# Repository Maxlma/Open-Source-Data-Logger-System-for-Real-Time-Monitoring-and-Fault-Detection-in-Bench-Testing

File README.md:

# 🧠 Smart Power Supply for Data Loggers

**Low-Cost / High-Precision UPS for Reliable Data Acquisition Systems**  
[Published in *Energies*, MDPI - DOI: [10.3390/en16010278](https://doi.org/10.3390/en16010278)]

## 📌 About the Project

This project presents the design and implementation of a **smart, low-cost, and high-precision power supply** system tailored for **data loggers** in experimental setups. It provides **uninterruptible power**, advanced **monitoring features**, and a **DIY-friendly open hardware** approach with robust performance under demanding conditions.

Developed by researchers from the **University of São Paulo (USP)** and the **University of Minho**, this power supply ensures uninterrupted operation even during AC power failures, thanks to an embedded UPS and smart control logic.

## ⚙️ Features

- 🔋 **AC/DC Dual Input** with seamless switching (UPS functionality)
- 📶 **Serial communication (UART)** with external devices
- 📺 **OLED Display** for real-time system status
- 🌡️ **Temperature monitoring** and **smart active cooling**
- 🔄 **Remote firmware update capability**
- 📏 Outputs: ±12V, 5V, 3.3V – bipolar and unipolar DC
- 🛡️ Protection: 3 internal fuses for AC input, DC section, and battery
- 🧠 Controlled by an **ATmega328PB** microcontroller
- 🧩 Fully documented open hardware – easily 3D printable case
- 💸 **Total cost under $150**

## 🧪 Experimental Results

Tests confirmed:

- **Switching time < 10 ms** between power sources  
- No voltage drop affecting operation under 0A, 1A, and 2A loads  
- Stable operation under AC loss scenarios  
- Precise voltage regulation and thermal control

## 📜 License

This project is licensed under the **Creative Commons BY 4.0**  
© 2022 by the authors. Reuse permitted with attribution.  
[License Details](https://creativecommons.org/licenses/by/4.0/)

## 👨‍🔬 Authors

- Márcio L. M. Amorim  
- Gabriel A. Ginja  
- João P. Carmo  
- Melkzedekue M. A. Moreira  
- Adriano A. G. Siqueira  
- José A. Afonso

## 📚 Citation

If you use this work, please cite:

> Amorim, M.L.M.; Ginja, G.A.; Carmo, J.P.; Moreira, M.M.A.; Siqueira, A.A.G.; Afonso, J.A.  
> *Low-Cost/High-Precision Smart Power Supply for Data Loggers.*  
> Energies 2023, 16, 278. DOI: [10.3390/en16010278](https://doi.org/10.3390/en16010278)

---

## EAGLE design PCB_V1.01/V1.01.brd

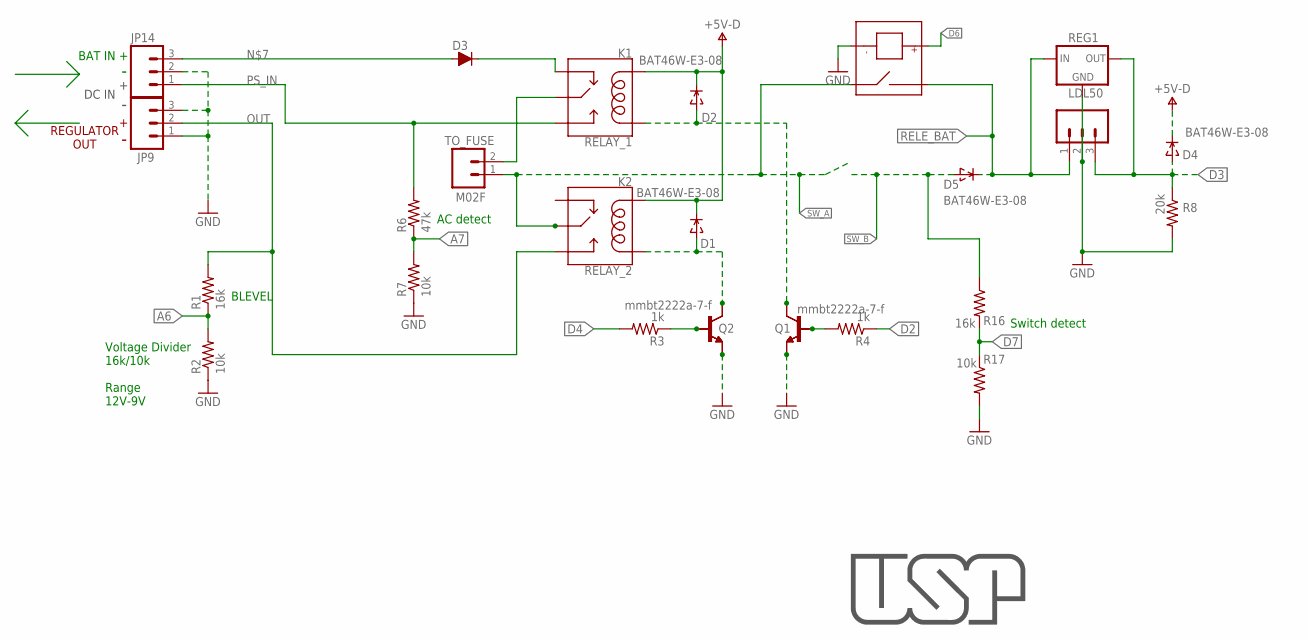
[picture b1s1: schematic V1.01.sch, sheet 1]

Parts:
7805: M03LOCK; 1X03_LOCK
D1, D2, D4, D5: BAT46W-E3-08; SOD-123
D3: DIODEFR; DIODE1.5A
JP9, JP14: M03; AK500
K1: RELAY_1; RELAY_G5LE
K2: RELAY_2; RELAY_G5LE
Q1, Q2: mmbt2222a-7-f; SOT23-3
Q3, Q4: TRANSISTOR-NPN-BC337; BC337
R1, R16: 16k; 0402
R2, R7, R17: 10k; 0402
R3, R4: 1k; 0402
R6: 47k; 0402
R8: 20k; 0402
REG1: LDL50; SOT223
RL1: RELAY_HE3621A0500; HE3621A
TO_FUSE: M02F; AK500M2

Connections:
+5V-D: D1.C, D2.C, D4.C, K1.2 (COIL1), K2.2 (COIL1); also elsewhere on the board
A6: R1.P$1 (1), R2.P$2 (2); also elsewhere on the board
A7: R6.P$1 (1), R7.P$2 (2); also elsewhere on the board
D2: R4.P$1 (1); also elsewhere on the board
D3: 7805.3, D4.A, R8.P$1 (1), REG1.2 (OUT), REG1.4 (OUT); also elsewhere on the board
D4: R3.P$2 (2); also elsewhere on the board
D6: RL1.P2; also elsewhere on the board
D7: R16.P$2 (2), R17.P$1 (1); also elsewhere on the board
GND: 7805.2, JP9.1, JP9.3, JP14.2, Q1.2 (E), Q2.2 (E), Q3.1 (E), Q4.1 (E), R2.P$1 (1), R7.P$1 (1), R8.P$2 (2), R17.P$2 (2), REG1.1 (GND), RL1.P3; also elsewhere on the board
unnamed: K1.1 (MAIN), TO_FUSE.2
unnamed: D2.A, K1.5 (COIL2), Q1.3 (C), Q4.3 (C)
unnamed: D1.A, K2.5 (COIL2), Q2.3 (C), Q3.3 (C)
unnamed: D3.A, JP14.3
unnamed: Q1.1 (B), Q4.2 (B), R4.P$2 (2)
unnamed: D3.C, K1.4 (NC)
OUT: JP9.2, K2.3 (NO), R1.P$2 (2)
PS_IN: JP14.1, K1.3 (NO), R6.P$2 (2)
RELE_BAT: 7805.1, D5.C, REG1.3 (IN), RL1.P1; also elsewhere on the board
STARTUP: Q2.1 (B), Q3.2 (B), R3.P$1 (1)
SW_A: K2.1 (MAIN), RL1.P4, TO_FUSE.1; also elsewhere on the board
SW_B: D5.A, R16.P$1 (1); also elsewhere on the board

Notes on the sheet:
BLEVEL
AC detect
Switch detect
BAT IN
REGULATOR OUT
DC IN
Voltage Divider 16k/10k Range 12V-9V

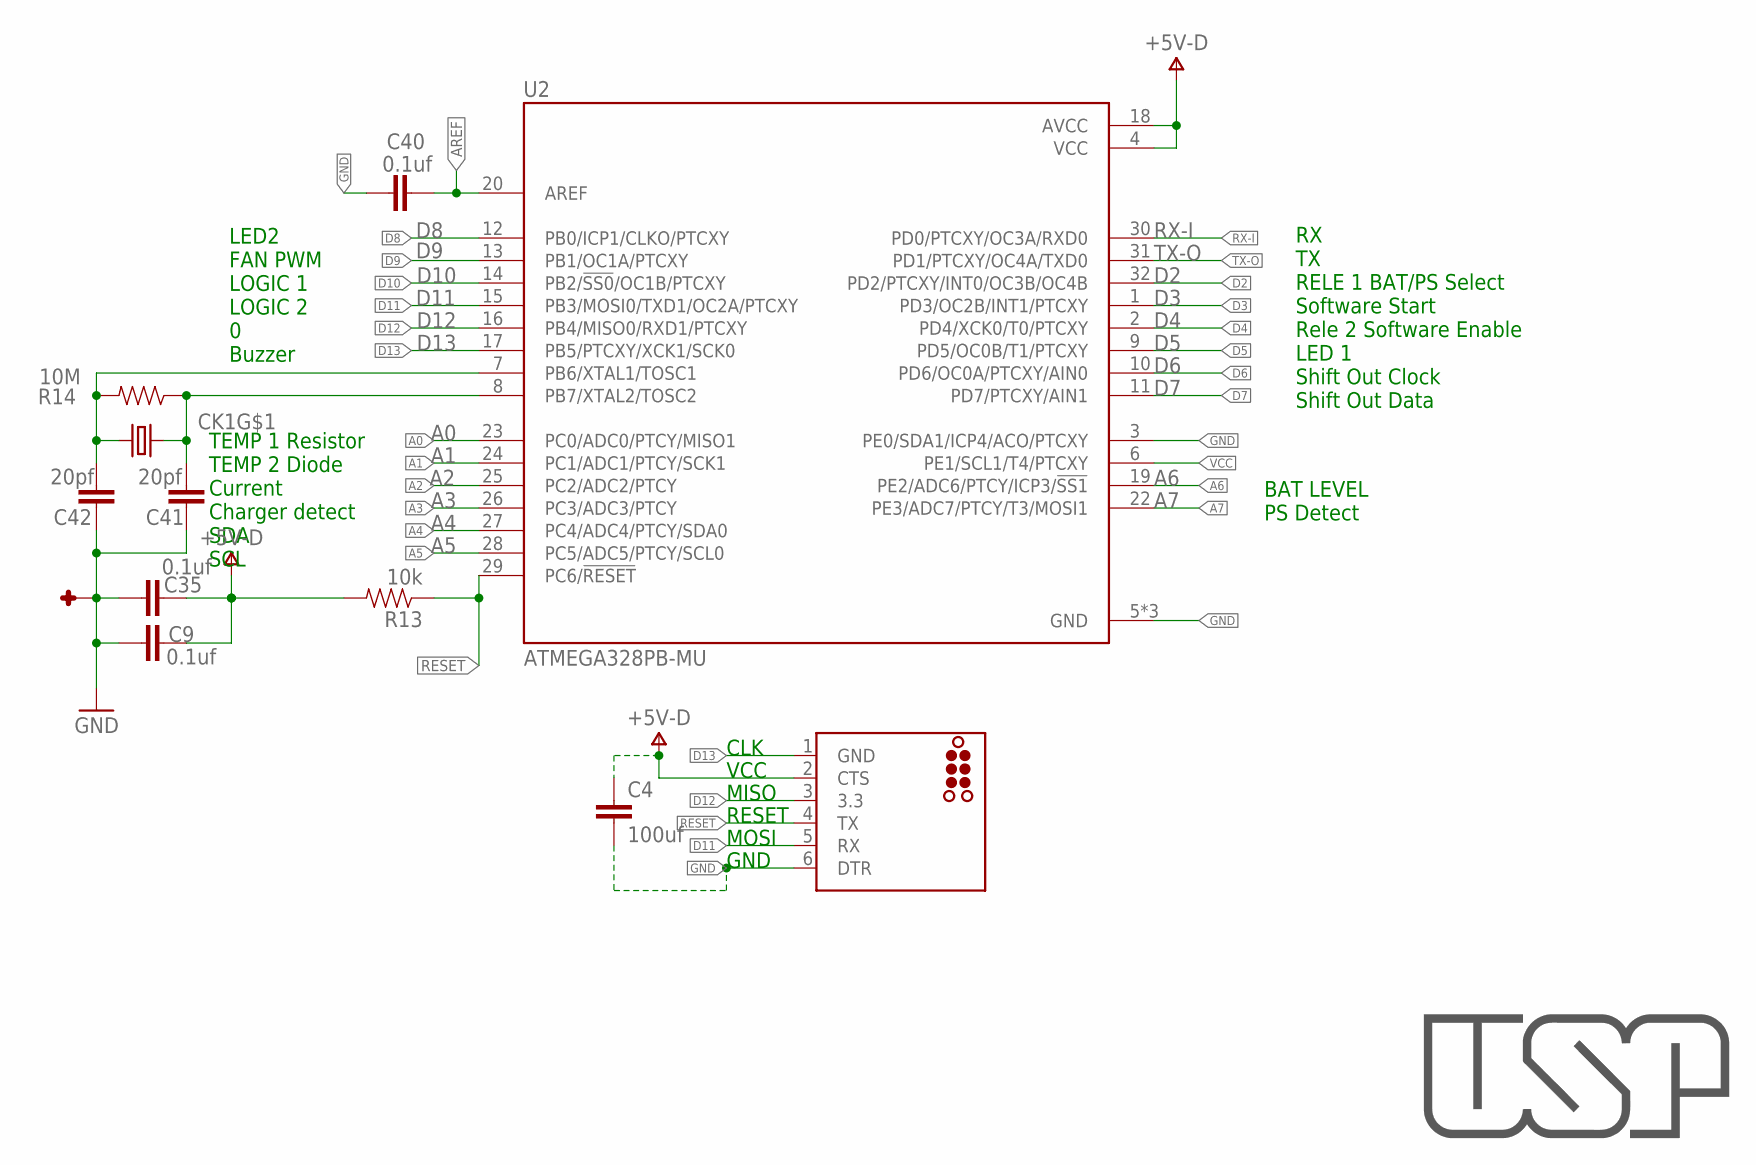
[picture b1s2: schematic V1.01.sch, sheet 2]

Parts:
C4: 100uf; 1206
C9, C35, C40: 0.1uf; 0402
C41, C42: 20pf; 0402
CK1: FA-238 16.0000MB-C3; 4-SMD@1
J10: DNP; TC2030-MCP-NL
R13: 10k; 0402
R14: 10M; 0402
U2: ATMEGA328PB-MU; QFN50P500X500X90-33N

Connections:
+5V-D: C4.1, C9.P$2 (2), C35.P$2 (2), J10.2 (CTS), R13.P$2 (2), U2.4 (VCC), U2.18 (AVCC); also elsewhere on the board
A0: U2.23 (PC0/ADC0/PTCY/MISO1); also elsewhere on the board
A1: U2.24 (PC1/ADC1/PTCY/SCK1); also elsewhere on the board
A2: U2.25 (PC2/ADC2/PTCY); also elsewhere on the board
A3: U2.26 (PC3/ADC3/PTCY); also elsewhere on the board
A4: U2.27 (PC4/ADC4/PTCY/SDA0); also elsewhere on the board
A5: U2.28 (PC5/ADC5/PTCY/SCL0); also elsewhere on the board
A6: U2.19 (PE2/ADC6/PTCY/ICP3/!SS1!); also elsewhere on the board
A7: U2.22 (PE3/ADC7/PTCY/T3/MOSI1); also elsewhere on the board
AREF: C40.P$1 (1), U2.20 (AREF)
D2: U2.32 (PD2/PTCXY/INT0/OC3B/OC4B); also elsewhere on the board
D3: U2.1 (PD3/OC2B/INT1/PTCXY); also elsewhere on the board
D4: U2.2 (PD4/XCK0/T0/PTCXY); also elsewhere on the board
D5: U2.9 (PD5/OC0B/T1/PTCXY)
D6: U2.10 (PD6/OC0A/PTCXY/AIN0); also elsewhere on the board
D7: U2.11 (PD7/PTCXY/AIN1); also elsewhere on the board
D8: U2.12 (PB0/ICP1/CLKO/PTCXY)
D9: U2.13 (PB1/OC1A/PTCXY); also elsewhere on the board
D10: U2.14 (PB2/!SS0!/OC1B/PTCXY)
D11: J10.5 (RX), U2.15 (PB3/MOSI0/TXD1/OC2A/PTCXY); also elsewhere on the board
D12: J10.3 (3.3), U2.16 (PB4/MISO0/RXD1/PTCXY)
D13: J10.1 (GND), U2.17 (PB5/PTCXY/XCK1/SCK0); also elsewhere on the board
GND: C4.2, C9.P$1 (1), C35.P$1 (1), C40.P$2 (2), C41.P$2 (2), C42.P$2 (2), CK1.GND1 (1), CK1.GND2 (1), J10.6 (DTR), U2.3 (PE0/SDA1/ICP4/ACO/PTCXY), U2.5 (GND), U2.21 (GND), U2.33 (GND); also elsewhere on the board
unnamed: C41.P$1 (1), CK1.P1 (1), R14.P$1 (1), U2.8 (PB7/XTAL2/TOSC2)
unnamed: C42.P$1 (1), CK1.P3 (2), R14.P$2 (2), U2.7 (PB6/XTAL1/TOSC1)
RESET: J10.4 (TX), R13.P$1 (1), U2.29 (PC6/!RESET!); also elsewhere on the board
RX-I: U2.30 (PD0/PTCXY/OC3A/RXD0); also elsewhere on the board
TX-O: U2.31 (PD1/PTCXY/OC4A/TXD0); also elsewhere on the board
VCC: U2.6 (PE1/SCL1/T4/PTCXY)

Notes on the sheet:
D11
RX TX RELE 1 BAT/PS Select Software Start Rele 2 Software Enable LED 1 Shift Out Clock Shift Out Data
LED2 FAN PWM LOGIC 1 LOGIC 2 0 Buzzer
TEMP 1 Resistor TEMP 2 Diode Current Charger detect SDA SCL
BAT LEVEL PS Detect
CLK VCC MISO RESET MOSI GND

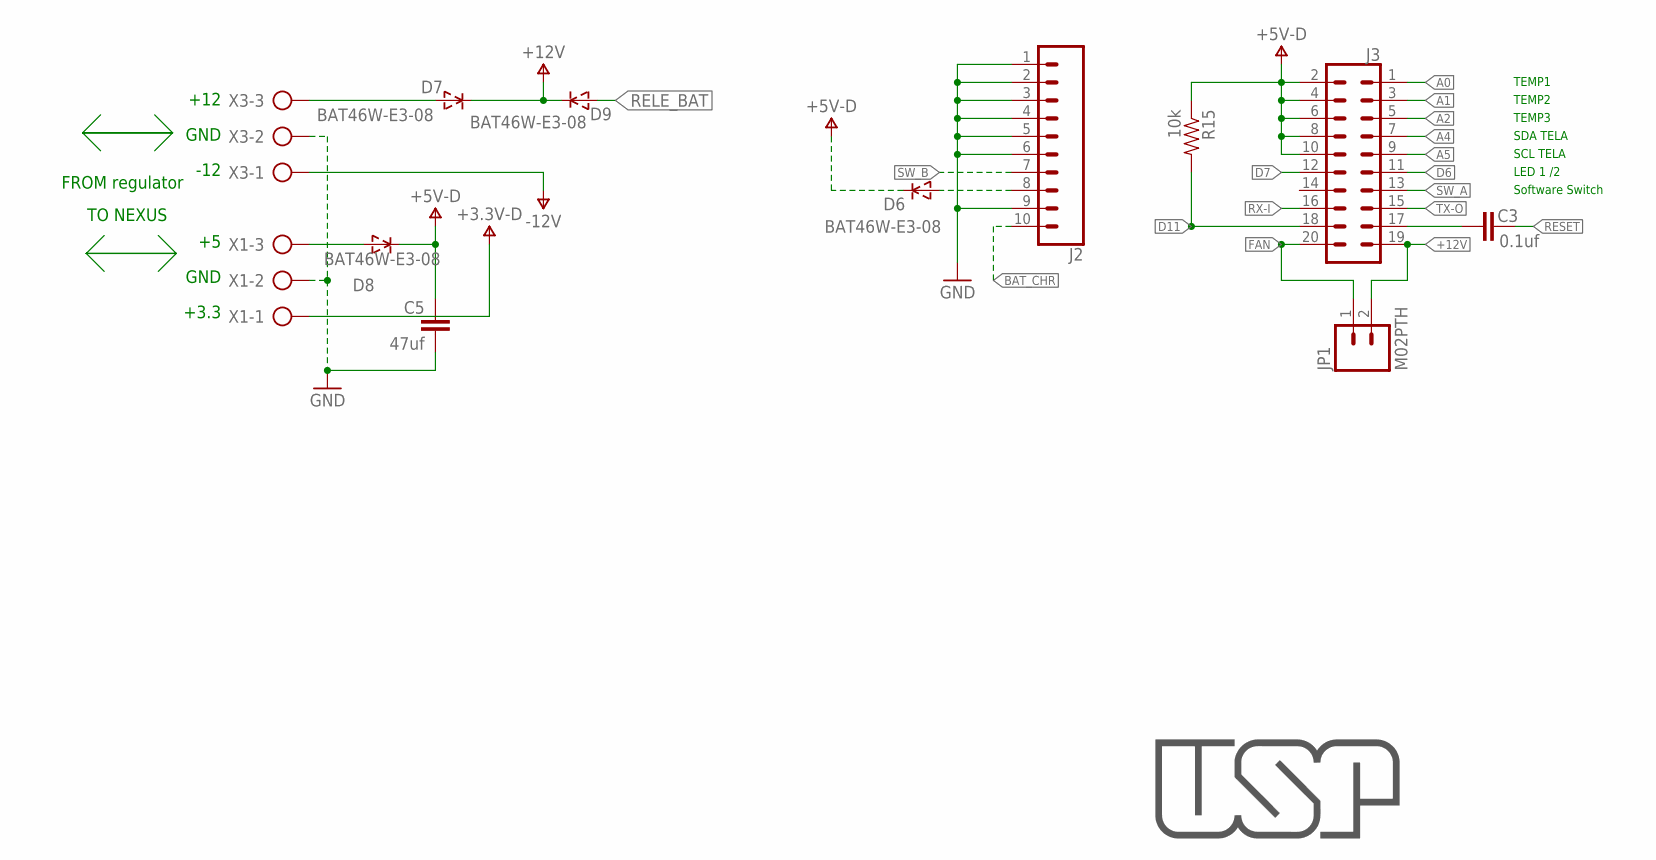
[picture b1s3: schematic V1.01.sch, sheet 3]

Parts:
C3: 0.1uf; 0402
C5: 47uf; 1206
D6, D7, D8, D9: BAT46W-E3-08; SOD-123
J2: CONN_10"; 1X10
J3: CONN_10X2; 2X10
JP1: M02PTH; 1X02
R15: 10k; 0402
X1, X3: AK500/3-H

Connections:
+3.3V-D: X1.1
+5V-D: C5.1, D6.C, D8.C, J3.2, J3.4, J3.6, J3.8, J3.10, R15.P$1 (1); also elsewhere on the board
+12V: D7.C, D9.C, J3.19, JP1.2
-12V: X3.1
A0: J3.1; also elsewhere on the board
A1: J3.3; also elsewhere on the board
A2: J3.5; also elsewhere on the board
A4: J3.7; also elsewhere on the board
A5: J3.9; also elsewhere on the board
BAT_CHR: J2.10; also elsewhere on the board
D6: J3.11; also elsewhere on the board
D7: J3.12; also elsewhere on the board
D11: J3.18, R15.P$2 (2); also elsewhere on the board
FAN: J3.20, JP1.1; also elsewhere on the board
GND: C5.2, J2.1, J2.2, J2.3, J2.4, J2.5, J2.6, J2.9, X1.2, X3.2; also elsewhere on the board
unnamed: D8.A, X1.3
unnamed: D6.A, J2.8
unnamed: D7.A, X3.3
RELE_BAT: D9.A; also elsewhere on the board
RESET: C3.P$2 (2); also elsewhere on the board
RESETT: C3.P$1 (1), J3.17
RX-I: J3.16; also elsewhere on the board
SW_A: J3.13; also elsewhere on the board
SW_B: J2.7; also elsewhere on the board
TX-O: J3.15; also elsewhere on the board

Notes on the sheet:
FROM regulator
+12 GND -12
TO NEXUS
TEMP1 TEMP2 TEMP3 SDA TELA SCL TELA LED 1 /2 Software Switch
+5 GND +3.3

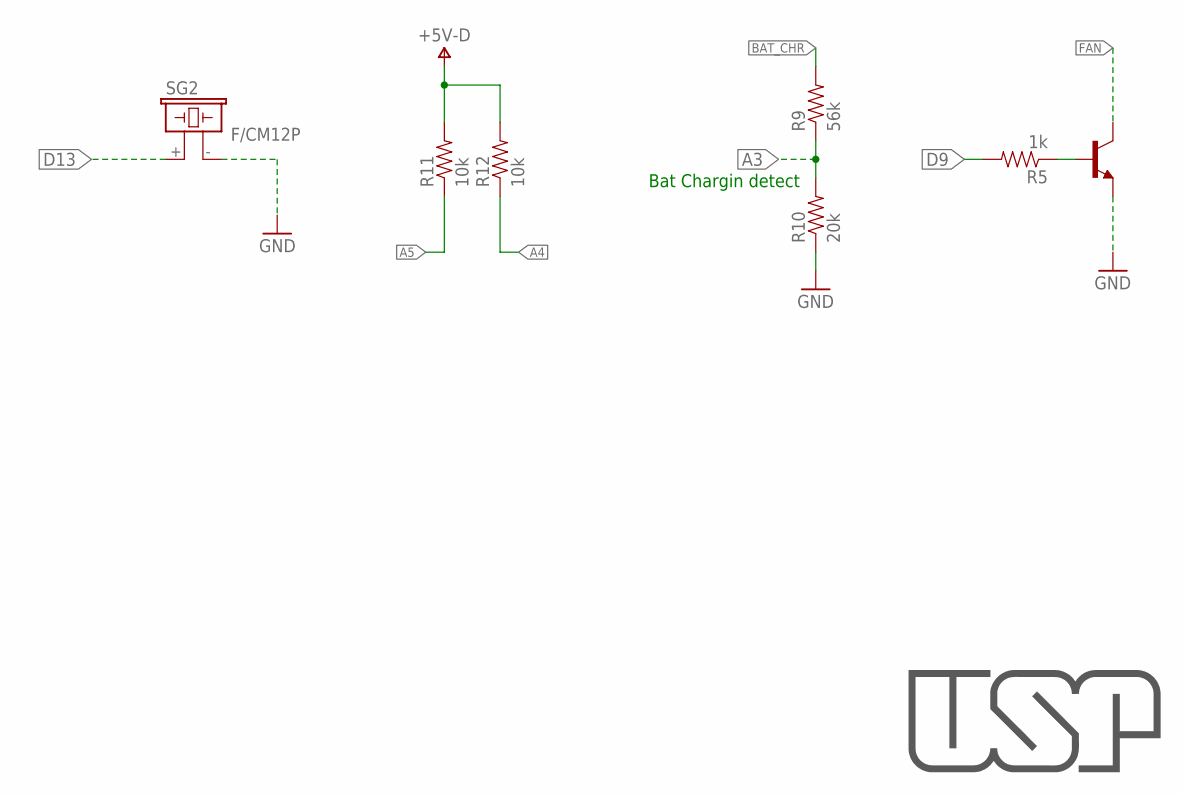
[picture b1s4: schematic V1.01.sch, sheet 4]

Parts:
Q5: TRANSISTOR-NPN-BC337; BC337
R5: 1k; 0402
R9: 56k; 0402
R10: 20k; 0402
R11, R12: 10k; 0402
SG2: F/CM12P

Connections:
+5V-D: R11.P$2 (2), R12.P$2 (2); also elsewhere on the board
A3: R9.P$1 (1), R10.P$2 (2); also elsewhere on the board
A4: R12.P$1 (1); also elsewhere on the board
A5: R11.P$1 (1); also elsewhere on the board
BAT_CHR: R9.P$2 (2); also elsewhere on the board
D9: R5.P$2 (2); also elsewhere on the board
D13: SG2.+ (1); also elsewhere on the board
FAN: Q5.3 (C); also elsewhere on the board
GND: Q5.1 (E), R10.P$1 (1), SG2.- (2); also elsewhere on the board
unnamed: Q5.2 (B), R5.P$1 (1)

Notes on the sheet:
Bat Chargin detect

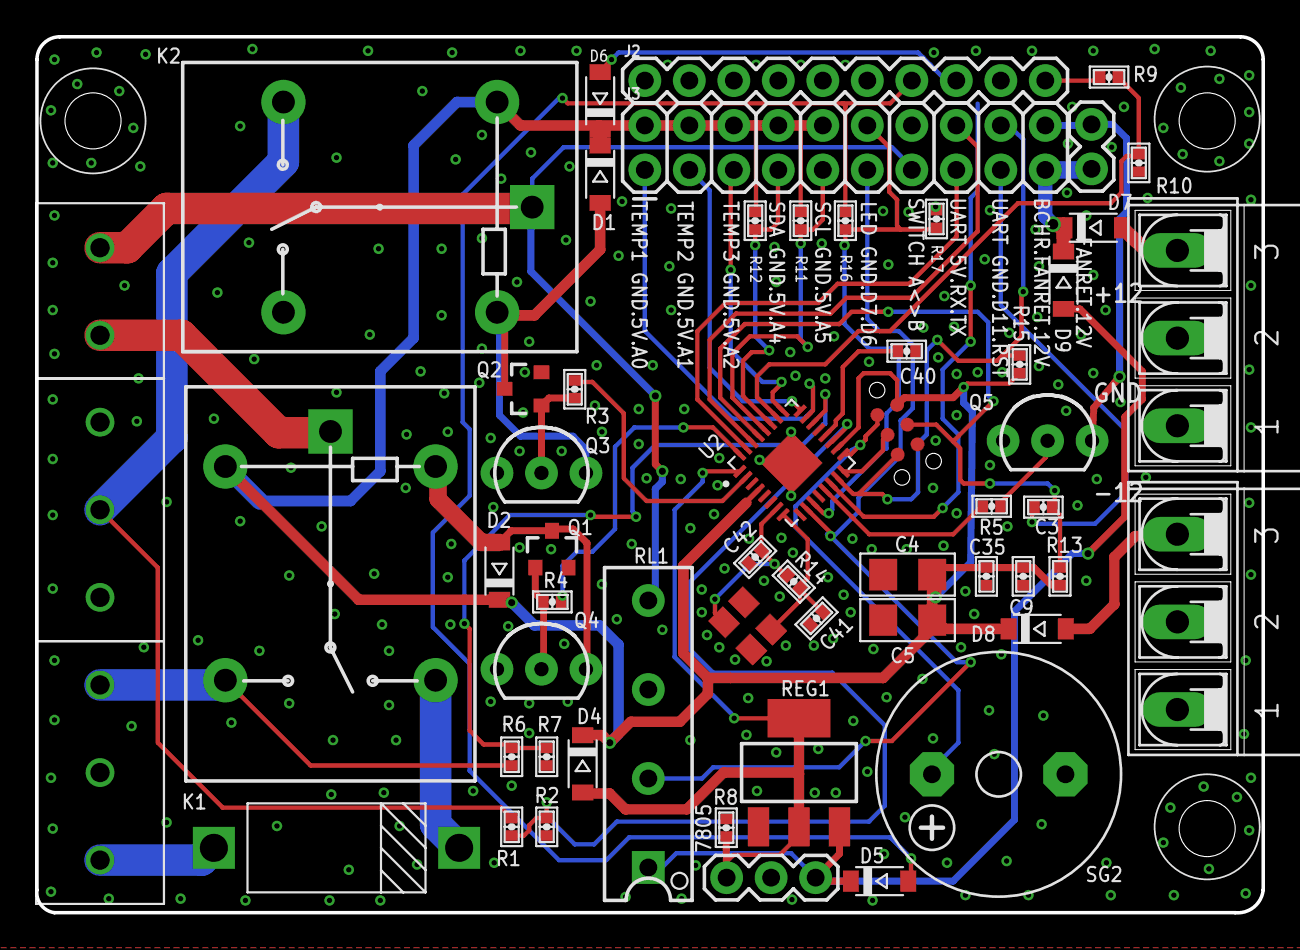
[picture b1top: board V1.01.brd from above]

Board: 2 copper layers, 70.0 x 50.0 mm, 57 parts (1 on the bottom side), 45 nets.

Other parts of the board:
U$5: NEXUS2

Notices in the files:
parts and their libraries:
MaxBYB: ©2009 ROFA.cz - modified and updated by Robert Darlington ‹rdarlington@gmail.com›
SparkFun-Connectors: Licensing: Creative Commons ShareAlike 4.0 International - https://creativecommons.org/licenses/by-sa/4.0
